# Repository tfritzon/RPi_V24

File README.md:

# RPi_V24
4 x V.24 (RS232) hat for RPi

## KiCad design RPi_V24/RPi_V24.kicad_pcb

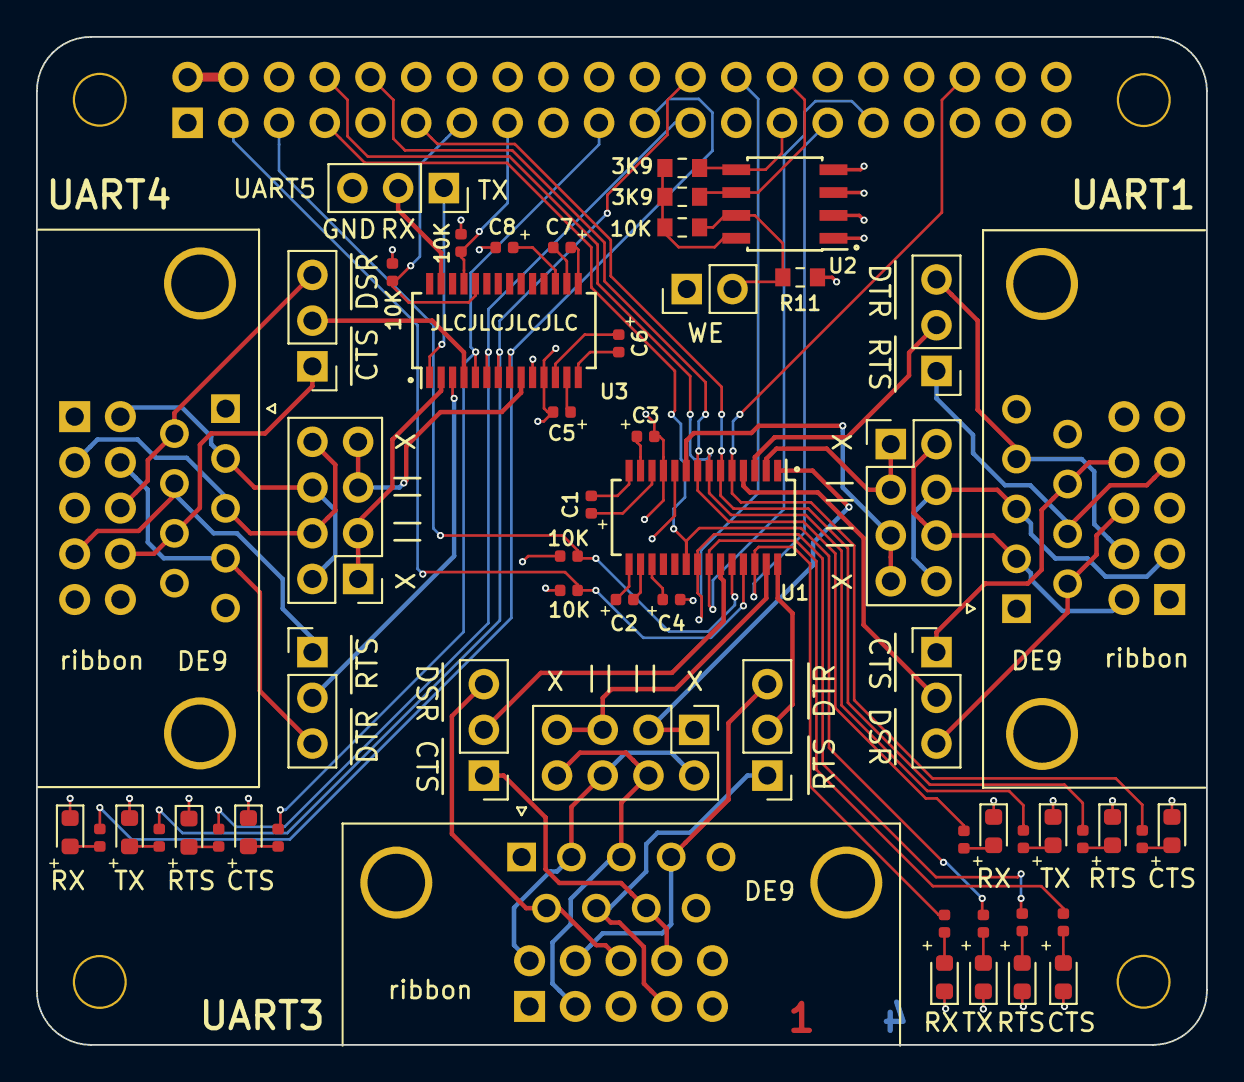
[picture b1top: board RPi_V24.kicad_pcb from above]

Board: 4 copper layers, 65.0 x 56.0 mm, 65 parts (1 on the bottom side), 79 nets.

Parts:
3K9, 3K9#2: 3.9K; R_0603_1608Metric_Pad0.84x1.00mm_HandSolder
10K: 10K; R_0603_1608Metric_Pad0.84x1.00mm_HandSolder
10K#2, 10K#3, 10K#4, 10K#5: 10K; R_0402_1005Metric
C1, C2, C3, C4, C5, C6, C7, C8: 1uF; C_0402_1005Metric
D1, D5, D9: RED; LED_0603_1608Metric
D2, D6, D10: GRN; LED_0603_1608Metric
D3, D7, D11: YEL; LED_0603_1608Metric
D4, D8, D12: BLU; LED_0603_1608Metric
H1, H2, H3, H4: 3mm_Mounting_Hole; NPTH_3mm_ID
J1, J2, J4: DB9_Male; DSUB-9_Male_Horizontal_P2.77x2.84mm_EdgePinOffset7.70mm_Hou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
J3: 40HAT; PinSocket_2x20_P2.54mm_Vertical
J5, J8, J13: Conn_02x04_Odd_Even; PinHeader_2x04_P2.54mm_Vertical
J6, J7, J10, J11, J14, J15: Conn_01x03; PinHeader_1x03_P2.54mm_Vertical
J9: CONN_01X02; PinHeader_1x02_P2.54mm_Vertical
J12: Conn_01x03_Female; PinSocket_1x03_P2.54mm_Vertical
J16, J17, J18: Conn_02x05_Odd_Even; IDC-Header_2x05_P2.54mm_Vertical
R1, R2, R3, R4, R5, R7, R9, R10, R12, R13, R14, R15: 2K2; R_0402_1005Metric
R11: DNP; R_0603_1608Metric_Pad0.84x1.00mm_HandSolder
U1, U3: MAX561; SSOP-28_3.9x9.9mm_P0.635mm
U2: CAT24C32; SOIC-8_3.9x4.9mm_P1.27mm

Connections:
/ID_SC_EEPROM: 3K9.2, J3.28, U2.6
/ID_SD_EEPROM: 3K9#2.2, J3.27, U2.5
/P3V3: 3K9.1, 3K9#2.1, 10K.1, U2.8
/P5V_HAT: J3.2, J3.4
CTS1: J3.36, R4.1, U1.5
CTS1C: J1.8, J7.1, J16.8
CTS1E: J7.2, U1.4
CTS3: J3.31, R10.1, U1.22
CTS3C: J2.8, J11.1, J17.8
CTS3E: J11.2, U1.23
CTS4: J3.19, R15.1, U3.5
CTS4C: J4.8, J15.1, J18.8
CTS4E: J15.2, U3.4
DSR1C: J1.6, J7.3, J16.6
DSR3C: J2.6, J11.3, J17.6
DSR4C: J4.6, J15.3, J18.6
DTR1C: J1.4, J6.3, J16.4
DTR3C: J2.4, J10.3, J17.4
DTR4C: J4.4, J14.3, J18.4
GND: 10K#3.2, 10K#5.2, C4.2, C8.2, D1.1, D2.1, D3.1, D4.1, D5.1, D6.1, D7.1, D8.1, D9.1, D10.1, D11.1, D12.1, J1.5, J2.5, J3.6, J3.9, J3.14, J3.20, J3.25, J3.30, J3.34, J3.39, J4.5, J9.1, J12.3, R11.2, U1.10, U2.1, U2.2, U2.3, U2.4, U3.10
unnamed: C1.1, U1.12
unnamed: C1.2, U1.14
unnamed: C2.1, U1.15
unnamed: C2.2, U1.16
unnamed: C3.1, U1.13
unnamed: C4.1, U1.17
unnamed: C5.1, U3.13
unnamed: C6.1, U3.12
unnamed: C6.2, U3.14
unnamed: C7.1, U3.15
unnamed: C7.2, U3.16
unnamed: C8.1, U3.17
unnamed: D1.2, R1.2
unnamed: D2.2, R2.2
unnamed: D3.2, R3.2
unnamed: D4.2, R4.2
unnamed: D5.2, R5.2
unnamed: D6.2, R7.2
unnamed: D7.2, R9.2
unnamed: D8.2, R10.2
unnamed: D9.2, R12.2
unnamed: D10.2, R13.2
unnamed: D11.2, R14.2
unnamed: D12.2, R15.2
unnamed: 10K.2, J9.2, R11.1, U2.7
P3V3_HAT: 10K#2.1, 10K#4.1, C3.2, C5.2, J3.1, U1.11, U3.11
RTS1: J3.11, R3.1, U1.6
RTS1C: J1.7, J6.1, J16.7
RTS1E: J6.2, U1.3
RTS3: J3.26, R9.1, U1.21
RTS3C: J2.7, J10.1, J17.7
RTS3E: J10.2, U1.28
RTS4: J3.23, R14.1, U3.6
RTS4C: J4.7, J14.1, J18.7
RTS4E: J14.2, U3.3
RXD1: J3.10, R2.1, U1.8
RXD1C: J1.2, J5.2, J5.6, J16.2
RXD1E: J5.5, J5.7, U1.9
RXD3: J3.29, R7.1, U1.26
RXD3C: J2.2, J8.2, J8.6, J17.2
RXD3E: J8.5, J8.7, U1.27
RXD4: J3.21, R13.1, U3.8
RXD4C: J4.2, J13.2, J13.6, J18.2
RXD4E: J13.5, J13.7, U3.9
RXD5E: J12.2, U3.27
SHDN1_3: 10K#2.2, J3.3, U1.25
SHDN4_5: 10K#4.2, J3.15, U3.25
TXD1: J3.8, R1.1, U1.7
TXD1C: J1.3, J5.4, J5.8, J16.3
TXD1E: J5.1, J5.3, U1.2
TXD3: J3.7, R5.1, U1.20
TXD3C: J2.3, J8.4, J8.8, J17.3
TXD3E: J8.1, J8.3, U1.1
TXD4: J3.24, R12.1, U3.7
TXD4C: J4.3, J13.4, J13.8, J18.3
TXD4E: J13.1, J13.3, U3.2
TXD5E: J12.1, U3.1
~EN1_3: 10K#3.1, J3.5, U1.24
~EN4_5: 10K#5.1, J3.13, U3.24

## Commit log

2021-09-08 First version
2021-09-09 Updated fills
2021-09-09 Now includes EN and SHDN for the transceivers.
2021-09-09 Adds layer identifiers
2021-09-09 Some final touches and some generated files.
2021-09-10 Silk screen adjustments.
2021-09-10 New gerbers because silk screen change
2021-09-10 Updated schema pdf.
2023-08-12 Adjusts some component and trace positions
2023-08-13 Converts to KiCAD 7
